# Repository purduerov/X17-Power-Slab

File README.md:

# X17-Power-Slab
Turns 48V into 12 V and 5 V

Whenever you make a new part, download the datasheet and save it here _**and**_ with the part in the parts library

Always pull other people's changes before beginning to work
`git pull`

Be sure to push your changes after  working on them. Run:
1. `git add .` to add any files in this directory or a subdirectory
or `git add -u` to add any modified files
2. (Optional) `git clean -nX` to see what ignored files can be removed
	`git clean -fX` removes ignored files (Eagle backups)
3. `git commit -m "helpful commit message"` with a description of the work that you did
4. `git push` to push your work to github

Other helpful commands
* `git status` says information about modified and staged files
* `git log` shows the recent commits of the repository
* `git log filename.extension` show the recent commits for just that file
* `git checkout first-couple-letter-of-commit-id` lets you go back to a previous version
* `git checkout master` brings you back to the latest commit
* `git tag` lists the tags
* `git tag -a orderX -m "the version of the board placed for the X'th order"` tag a specific commit
* `git push --tags` needed to push tags to remote
* `git show orderX` show the commit log for the given tag
* `git checkout orderX` go back and interact with the files at the tagged commit

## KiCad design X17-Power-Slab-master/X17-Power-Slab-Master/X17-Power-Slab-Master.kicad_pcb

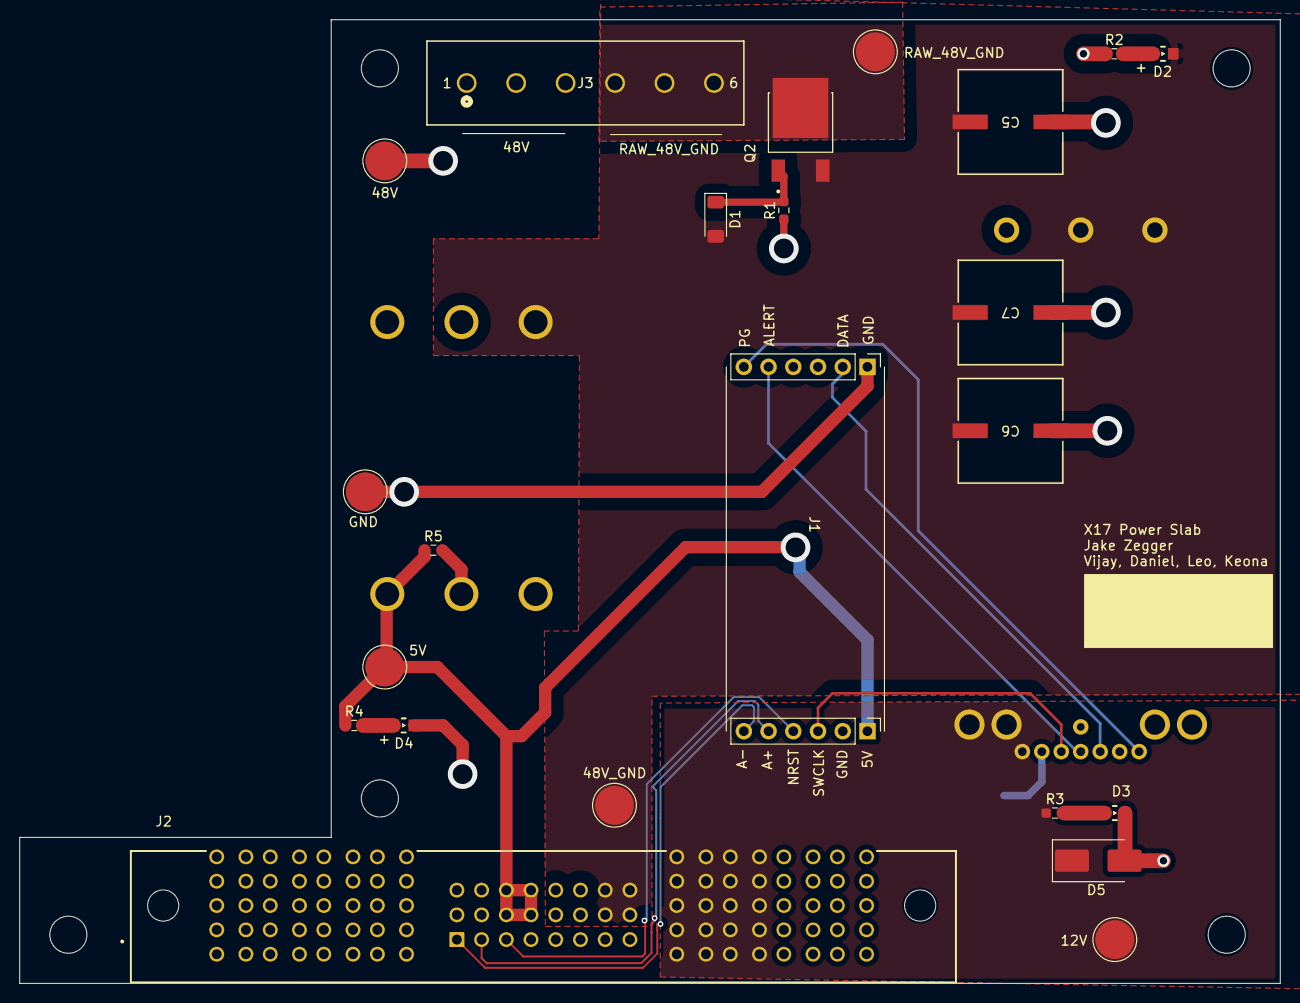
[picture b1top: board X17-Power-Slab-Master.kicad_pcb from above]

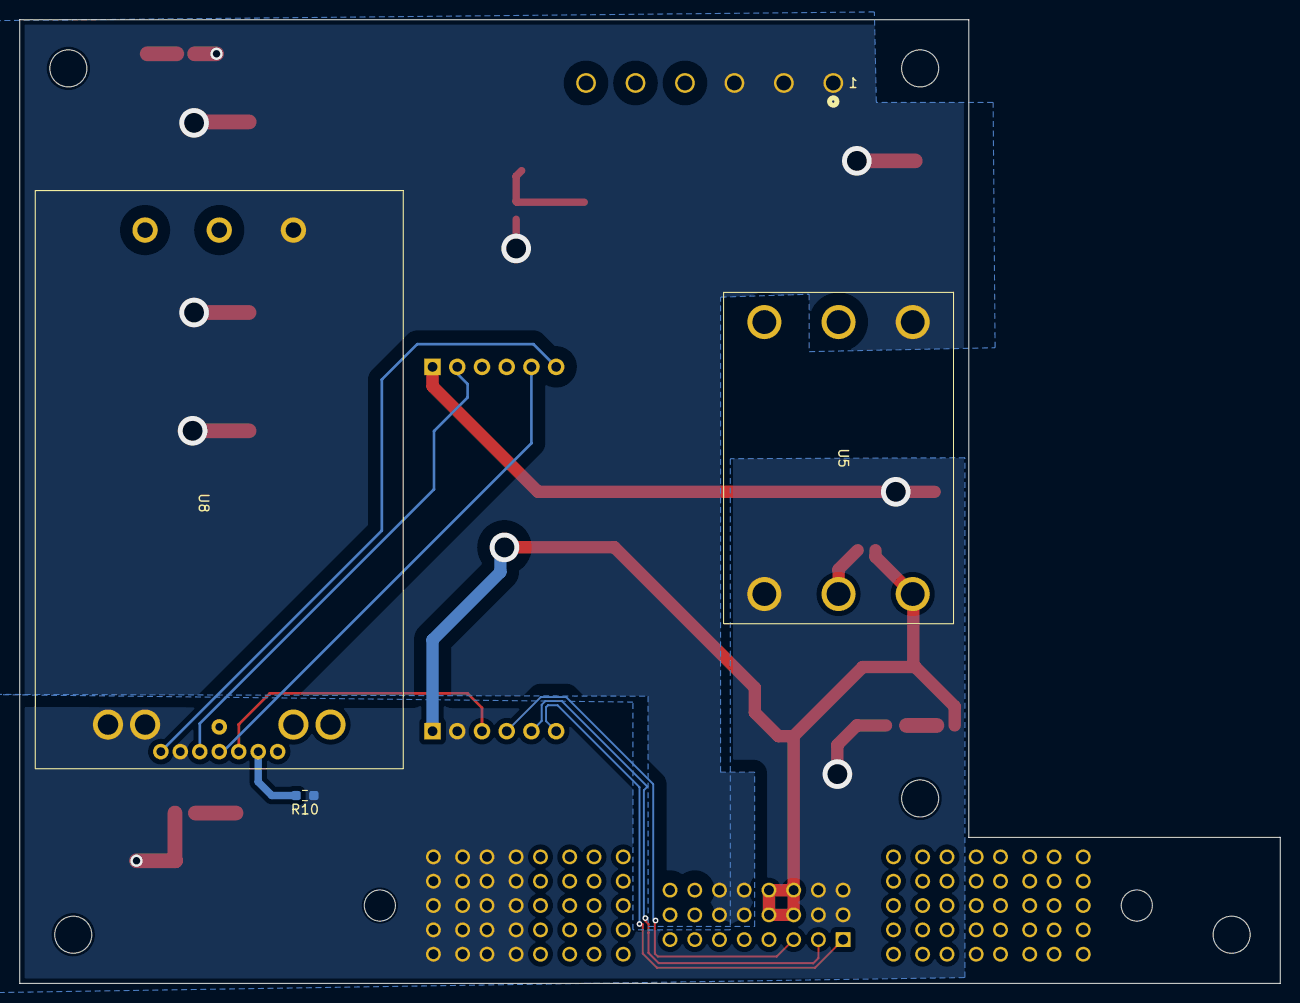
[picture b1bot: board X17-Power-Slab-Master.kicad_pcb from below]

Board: 2 copper layers, 129.5 x 99.0 mm, 31 parts (8 on the bottom side), 19 nets.

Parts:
C5, C6, C7: C; CAP_50TPV_10x10.5_RBY
D1: PZU15B3A,115; D_MiniMELF
D2: 48V; WL-SMCW_0805
D3: 12V; WL-SMCW_0805
D4: 5V; WL-SMCW_0805
D5: D_TVS; D_SMB_Handsoldering
H1, H1#2, H1#3, H3, H4: 6-32-HOLE
J1: Conn_01x12_Pin; Data Conversion two 1x6
J2: ET60T-D04-3-08-D04-X-R1-S; SAMTEC_ET60T-D04-3-08-D04-S-R1-S
J3: 796636-6; CON6_P5MM_VER_TERM-BLK_TYC
Q2: TSM340N06CP ROG; TRANS_TSM340N06CPROG
R1: 100k; R_0603_1608Metric_Pad0.98x0.95mm_HandSolder
R2: 3k; R_0603_1608Metric_Pad0.98x0.95mm_HandSolder
R3: 250; R_0603_1608Metric_Pad0.98x0.95mm_HandSolder
R4: 150; R_0603_1608Metric_Pad0.98x0.95mm_HandSolder
R5: 402k; R_0603_1608Metric_Pad0.98x0.95mm_HandSolder
R10: 10k; R_0603_1608Metric_Pad0.98x0.95mm_HandSolder
TP2, TP3, TP5, TP6, TP14, TP15: TestPoint; TestPoint_Pad_D4.0mm
U5: PKU5000e
U8: BMR4910203851

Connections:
5V: J1.7, J2.11, J2.12, J2.19, J2.20, R4.1, R5.1, TP14.1, U5.6 (Out+)
12V: D5.1 (A1), J2.P05_1 (P05), J2.P05_2, J2.P05_3, J2.P05_4, J2.P05_5, J2.P05_6, J2.P05_7, J2.P05_8, J2.P05_9, J2.P05_10, J2.P06_1 (P06), J2.P06_2, J2.P06_3, J2.P06_4, J2.P06_5, J2.P06_6, J2.P06_7, J2.P06_8, J2.P06_9, J2.P06_10, R3.1, TP3.1, U8.7 (+Out), U8.8 (+Out), U8.15 (SA0/+SENSE)
12V_5V_GND: D3.1, D4.1, D5.2 (A2), J1.1, J1.8, J2.09, J2.10, J2.17, J2.18, J2.P07_1 (P07), J2.P07_2, J2.P07_3, J2.P07_4, J2.P07_5, J2.P07_6, J2.P07_7, J2.P07_8, J2.P07_9, J2.P07_10, J2.P08_1 (P08), J2.P08_2, J2.P08_3, J2.P08_4, J2.P08_5, J2.P08_6, J2.P08_7, J2.P08_8, J2.P08_9, J2.P08_10, R10.1, TP15.1, U5.4 (Out-), U8.4 (-Out), U8.5 (-Out), U8.10 (-SENSE)
48V: C5.1, C6.1, C7.1, J2.13, J2.14, J2.21, J2.22, J3.1, J3.2, J3.3, R1.1, R2.1, TP5.1, U5.1 (+In), U8.1 (+In)
48V_GND: C5.2, C6.2, C7.2, D1.2 (A), D2.1, J2.15, J2.16, J2.23, J2.24, Q2.3, TP2.1, U5.3 (In-), U8.2 (RC), U8.3 (-In)
A+: J1.11, J2.02
A-: J1.12, J2.01
ALERT1: J1.5, U8.12 (SALERT)
DATA: J1.2, U8.11 (SDA)
NRST_PSB: J1.10, J2.03
unnamed: D1.1 (K), Q2.1, R1.2
unnamed: D2.2, R2.2
unnamed: D3.2, R3.2
unnamed: D4.2, R4.2
unnamed: R5.2, U5.5 (Vadj)
unnamed: R10.2, U8.14 (SA0/SA1)
PG: J1.6, U8.9 (PG/CTRL)
RAW_48V_GND: J3.4, J3.5, J3.6, Q2.2, TP6.1
SWCLK: J1.9, U8.13 (SCL)

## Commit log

2024-10-23 Changes 10/23
    Schematic partially done
2024-10-26 Alumni Design Review Pre-Changes
    No 48V to 5V Schematic, unfinished STM32 connections, DRC issues, flags not neat.
2024-10-26 Latest Updated Alumni Design Review
    Added 48V to 5V DC DC Converter Symbol. Footprint still needed.
2024-10-26 Clarifications
    Added clarifications for trim and resistor meant for adjusting output voltage.
2024-11-07 for daniel
2024-11-07 added board dimensions
2024-11-09 STM32 Pinout
    Complete STM32 pinout added without connector (need to find model and download)
2024-11-21 Schematic Updates
    #SlayedTheDayAway
2024-11-21 Schematic Full Update
    Probs can start pacing after this.
    Diode on RVP changed,
    Button changed
    Reverse voltage updated
    Symbols updated to remove DRCs
    GNDs changed
2024-11-22 Initial Placements
    Issue - NRST_PSB is apparently ground flag
2024-11-23 Final First(?) Draft
    NRST is stuck to general ground for whatever reason.
    Test points wont connect for the life of me, will look @ in morning, will have sample plan.
    Idea is there, really want to plan it out better 2nd time around. Alumni will give good tips!
2024-12-14 Routes
    Cannot fill the polygons for some reason
2024-12-14 new dimensions
2024-12-15 Power traces update
    I think I'm getting the idea of power traces needed?
2024-12-17 Change to combined 12V 5V gnd
2024-12-18 Power slab delivery changes
    Not done yet
2024-12-19 More connections
    Fixing errors and thermal relief
2024-12-19 Connectors and Testpoints for all components
    Errors with thermal relief in my capacitors
2024-12-19 Final Power Board
    There is an error of a missing connection for two of the test points 12_5V_GND for the 5V brick and the 12V brick and I cant resolve the DRC error.
2024-12-19 Final Board 2
    See prior description
2024-12-20 Connector pins renamed and attempt @ fixing airwires for 5V Brick
    Still don't understand why the airwire from 5V to 12V_5V_GND test point exists, I also now have airwires across all my P08_1 pins despite the same set up existing for 12V.
2024-12-29 Minor Edits
    Some layout edits, got rid of stm, not done yet
2024-12-30 final for 12/30 meeting
2024-12-30 Board review 12/30
2025-01-04 changes 1/3/25
2025-01-09 changes 1/9/25 AMs
2025-01-09 silkscreen + pinout fixes
2025-01-09 some pinout changes
2025-01-10 all ordered!
2025-03-28 changes, added 12V connections to all big samtec pins
2025-03-28 march 28 changes pt2
2025-03-28 power slab v2 manufacturing
2025-03-29 Traces fixed
    Traces for data conversion spaced to be at least .16mm apart
2025-03-30 changes post manufacturing update march 30
2025-09-20 start of board etc
2025-09-20 Revert "start of board etc"
    This reverts commit dacd3e492f62288f995083086c881b39b620ec2d.
